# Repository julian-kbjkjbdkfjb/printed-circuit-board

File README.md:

# printed circuit board
my first KiCad project!

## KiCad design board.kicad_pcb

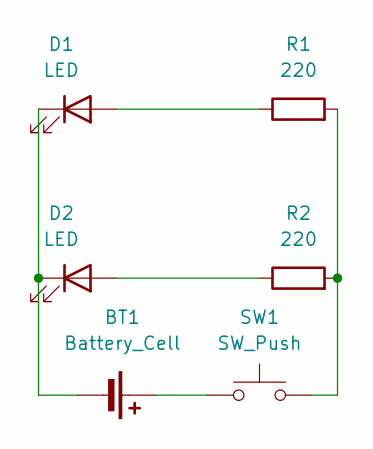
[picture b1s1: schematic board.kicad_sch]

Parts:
BT1: Battery_Cell; BatteryHolder_Keystone_3034_1x20mm
D1, D2: LED; LED_D5.0mm
R1, R2: 220; R_Axial_DIN0207_L6.3mm_D2.5mm_P7.62mm_Horizontal
SW1: SW_Push; SW_PUSH_6mm

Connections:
unnamed: BT1.1 (+), SW1.1
unnamed: BT1.2 (-), D1.1 (K), D2.1 (K)
unnamed: D1.2 (A), R1.1
unnamed: D2.2 (A), R2.1
unnamed: R1.2, R2.2, SW1.2

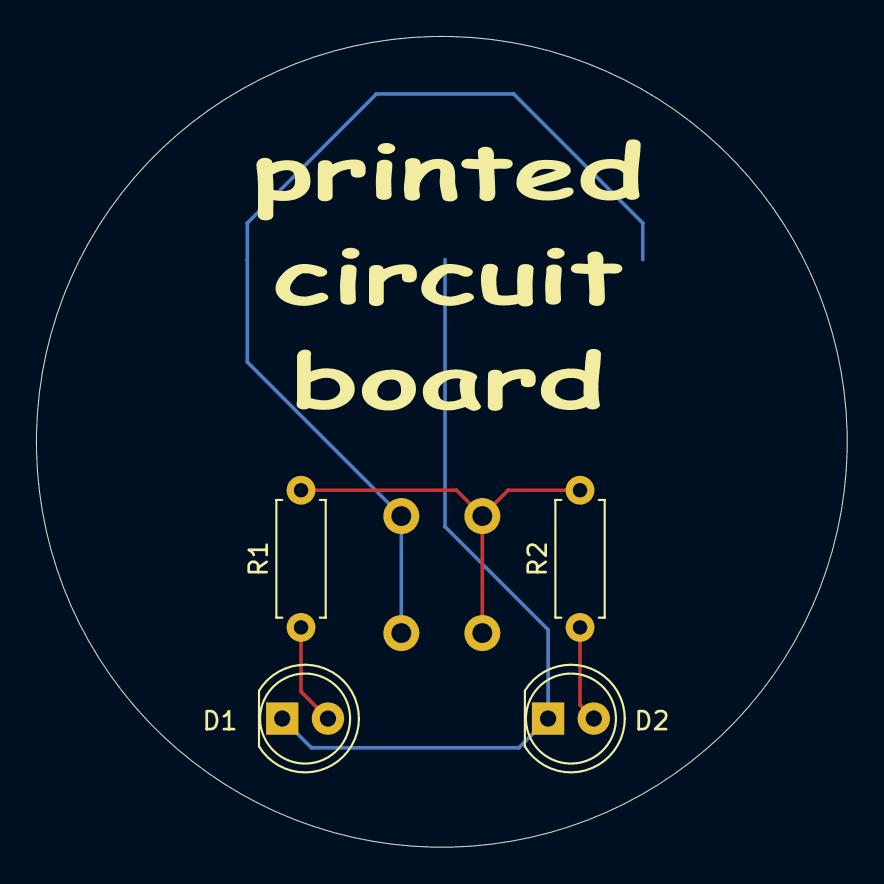
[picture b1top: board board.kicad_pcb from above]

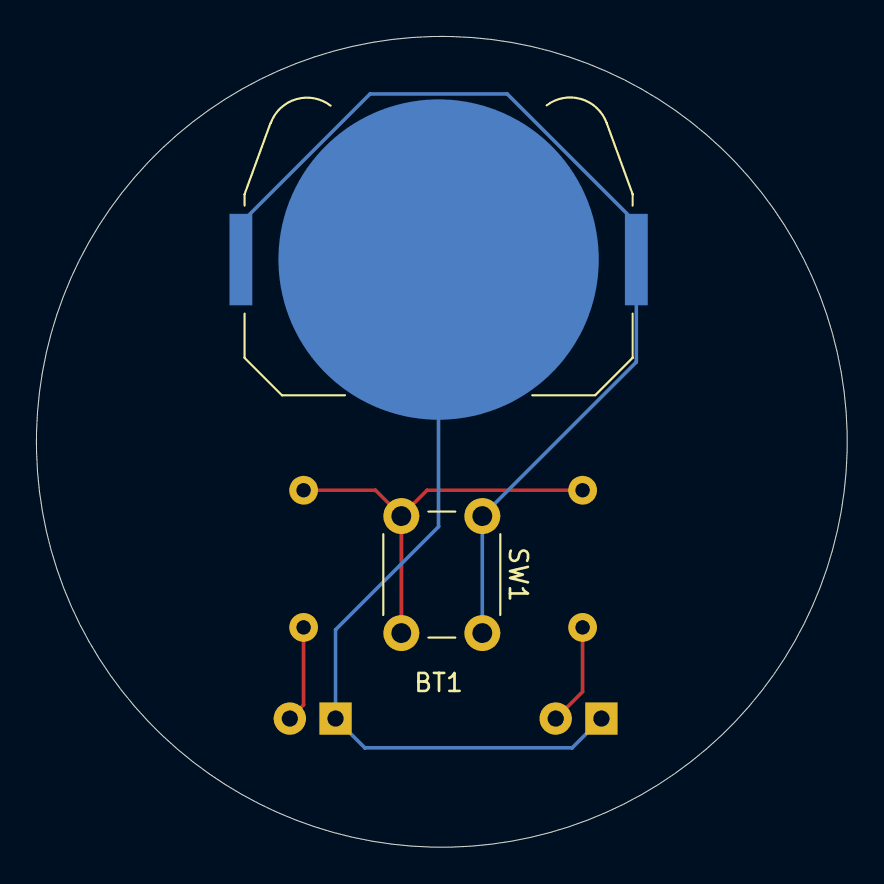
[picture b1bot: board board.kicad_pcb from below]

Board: 2 copper layers, 45.0 x 45.0 mm, 6 parts (2 on the bottom side), 5 nets.

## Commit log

2025-06-02 Rename PrintedCircuitBoard.zip to production/PrintedCircuitBoard.zip
